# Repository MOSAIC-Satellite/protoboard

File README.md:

# ProtoBoard

This is the repository for MOSAIC's ProtoBoard.

For detailed information on the ProtoBoard, check out its core documentation [here](https://www.mosaicsat.org/core_documentation/hardware/protoboard/).

To get your own MOSAIC ProtoBoard, visit the MOSAIC fabrication guide [here](https://www.mosaicsat.org/getting_mosaic/).

## Current Features

*Newest board version: 1.0*

| **Feature** |
| :----------- |
| 6x Qwiic connectors |
| 6x prototyping board matricies with I2C access |
| 24x mounting holes for SparkFun I2C/Qwiic sensors |

## Planned Changes

There are currently no planned changes for the ProtoBoard. 

Have an idea to make this board better? We'd love to hear it! 

## Change Log

You can find the change log for the ProtoBoard on MOSAIC's website [here](https://www.mosaicsat.org/core_documentation/hardware/protoboard/change_log/).

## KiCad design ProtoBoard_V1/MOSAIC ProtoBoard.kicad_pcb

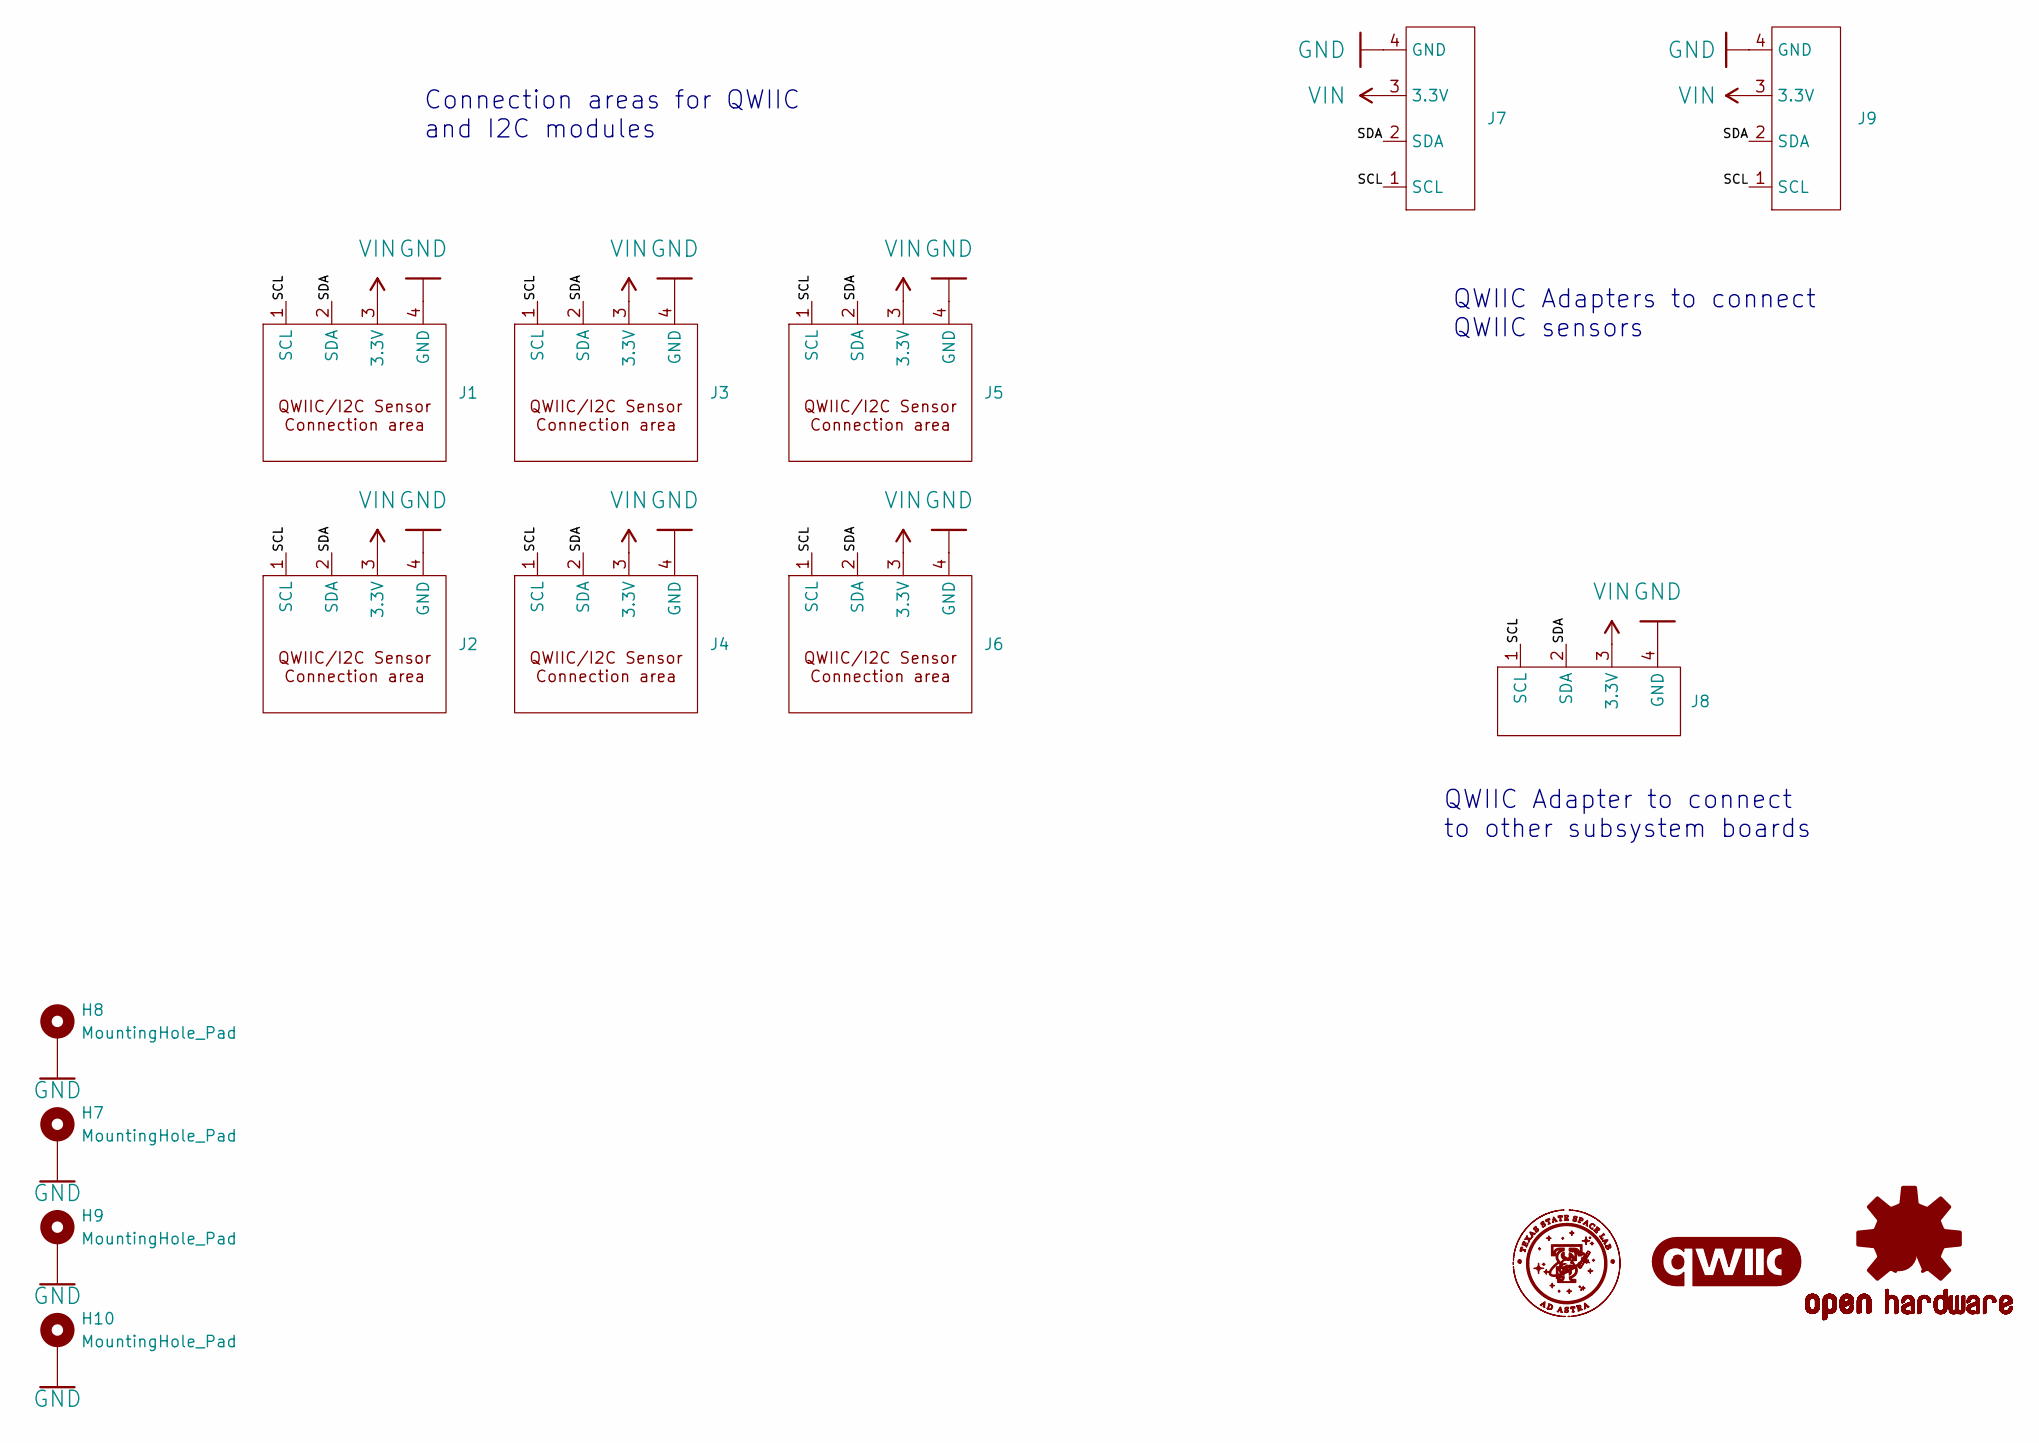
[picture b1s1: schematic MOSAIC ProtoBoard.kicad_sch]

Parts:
H7, H8: MountingHole_Pad; MountingHole_3.2mm_M3_Pad
H9, H10: MountingHole_Pad; MountingHole_3.2mm_Pad_Oval
J1, J2, J3, J4, J5, J6: QWIIC_Sensor_CONN
J7, J8, J9: Qwiic Adapter; QWIIC_2_Adapter
LOGO1: QWIIC_8MM
LOGO2: OSHW-LOGO-L

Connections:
/SCL: J1.1 (SCL), J2.1 (SCL), J3.1 (SCL), J4.1 (SCL), J5.1 (SCL), J6.1 (SCL), J7.1 (SCL), J8.1 (SCL), J9.1 (SCL)
/SDA: J1.2 (SDA), J2.2 (SDA), J3.2 (SDA), J4.2 (SDA), J5.2 (SDA), J6.2 (SDA), J7.2 (SDA), J8.2 (SDA), J9.2 (SDA)
GND: H7.1, H8.1, H9.1, H10.1, J1.4 (GND), J2.4 (GND), J3.4 (GND), J4.4 (GND), J5.4 (GND), J6.4 (GND), J7.4 (GND), J8.4 (GND), J9.4 (GND)
VIN: J1.3 (3.3V), J2.3 (3.3V), J3.3 (3.3V), J4.3 (3.3V), J5.3 (3.3V), J6.3 (3.3V), J7.3 (3.3V), J8.3 (3.3V), J9.3 (3.3V)

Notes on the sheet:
Connection areas for QWIIC and I2C modules
QWIIC Adapters to connect QWIIC sensors
QWIIC Adapter to connect to other subsystem boards

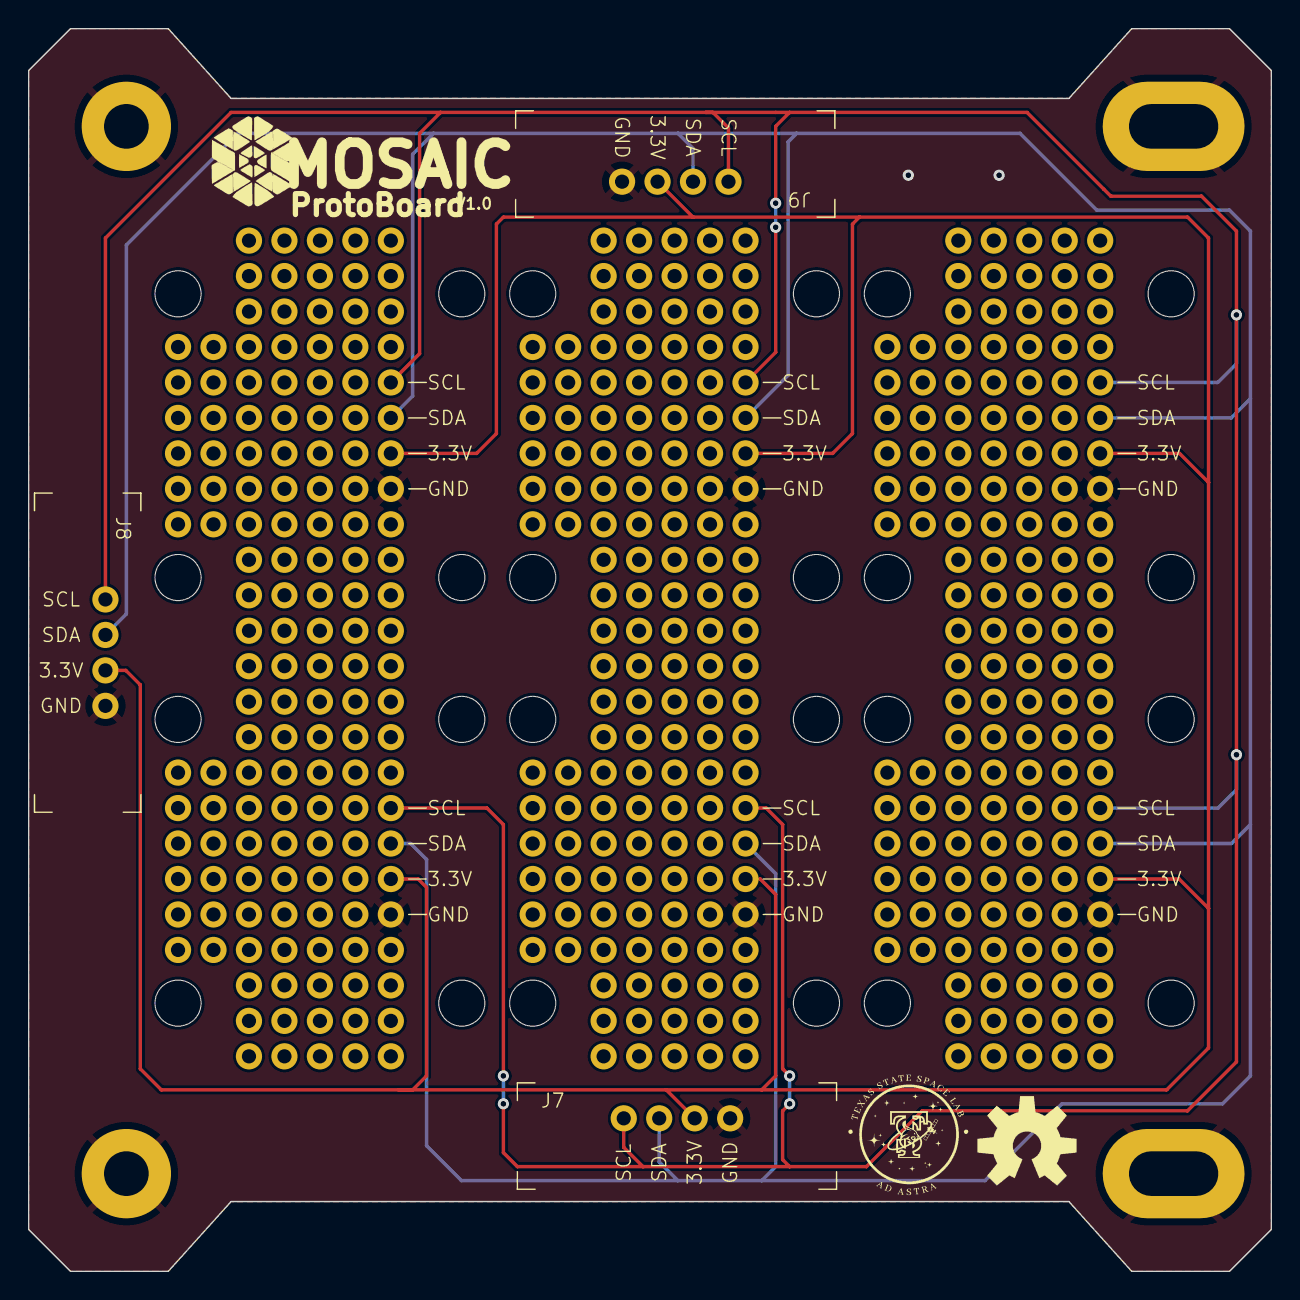
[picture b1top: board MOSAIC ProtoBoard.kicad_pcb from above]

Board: 2 copper layers, 89.0 x 89.0 mm, 14 parts (0 on the bottom side), 4 nets.

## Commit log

2024-08-07 Create LICENSE.txt
    Create copyright for ProtoBoard repository.
2024-08-07 Initial Upload
    Initial upload of all files for the MOSAIC ProtoBoard repository.
2025-04-29 Updated to KiCad 9.0
2025-04-29 Finished session
2025-05-30 Created new edge cut
    Created new edge cut for the board based on new standard size
2025-05-30 Add mounting holes to schematic
2025-05-30 Added circle mount holes to PCB
2025-05-30 Add mounts to schem and board
2025-05-30 Positioning and routing
2025-05-30 Finished placement and routing
2025-06-16 made fab files
